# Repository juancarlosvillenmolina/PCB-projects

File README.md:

# PCB-projects

This repository contains various PCB (Printed Circuit Board) projects that I have worked on. Each project includes design files, schematics, and documentation to help you understand the purpose and functionality of the PCB.

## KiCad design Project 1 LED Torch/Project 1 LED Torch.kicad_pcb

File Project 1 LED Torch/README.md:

# Project 1 — LED Torch

PCB image used in the project:

<!-- If the relative path doesn't work in your viewer, you can use an absolute Windows path (not recommended for shared repositories): -->
<!--  -->

Description:

This repository contains the files related to the PCB design for the LED Torch project. The image above shows the main PCB.

Additional images:

- 3D View (front):

- 3D View (back):

- Schematic:

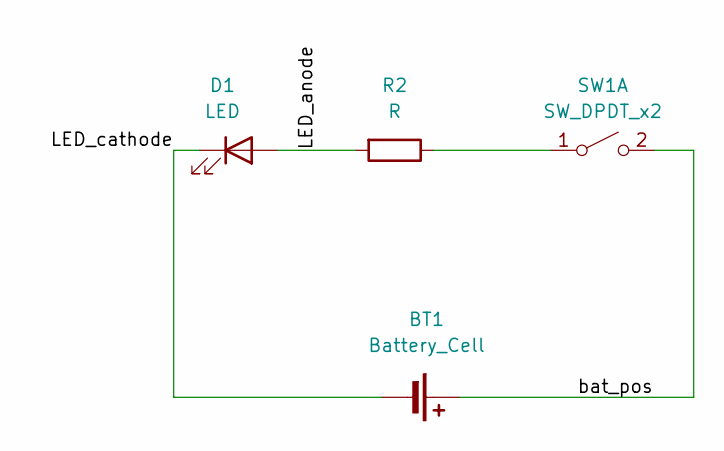
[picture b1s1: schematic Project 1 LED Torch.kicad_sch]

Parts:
BT1: Battery_Cell; BatteryHolder_Keystone_1058_1x2032
D1: LED; LED_D5.0mm
R2: R; R_Axial_DIN0204_L3.6mm_D1.6mm_P7.62mm_Horizontal
SW1: SW_DPDT_x2; SW_TH_Tactile_Omron_B3F-100x

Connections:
/LED_anode: D1.2 (A), R2.2
/LED_cathode: BT1.2 (-), D1.1 (K)
/bat_pos: BT1.1 (+), SW1.2 (B)
unnamed: R2.1, SW1.1 (A)

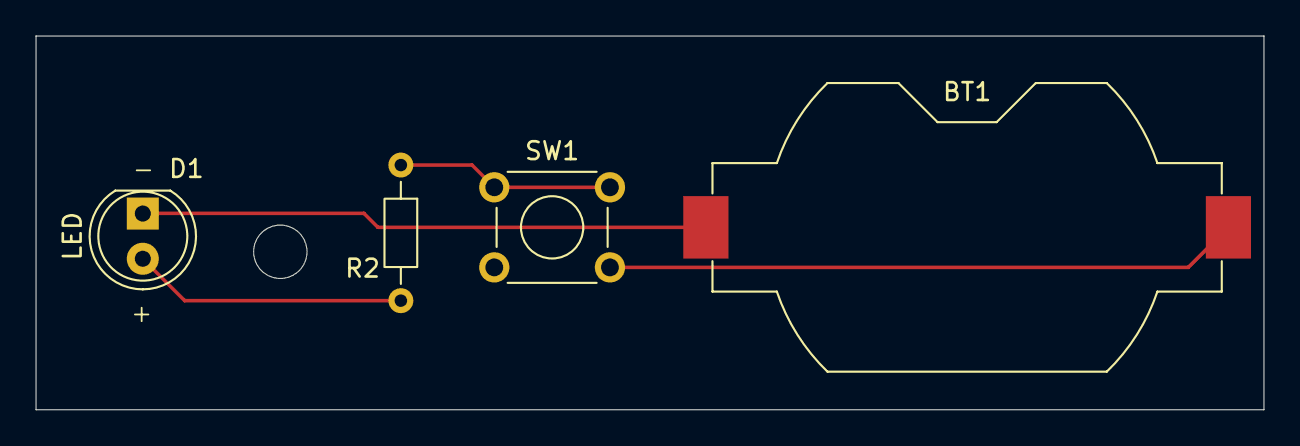
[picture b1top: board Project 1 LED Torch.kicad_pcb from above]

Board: 2 copper layers, 69.0 x 21.0 mm, 4 parts (0 on the bottom side), 4 nets.

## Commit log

2025-10-19 LED Torch
